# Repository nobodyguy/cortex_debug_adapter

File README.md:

# cortex_debug_adapter
Adapts the standard 10-pin 0.05" pitch ARM Cortex JTAG/SWD connector to a 7-pin 0.1" pitch row.\
Works great with the [greyhound probe](https://github.com/nobodyguy/greyhound_probe).

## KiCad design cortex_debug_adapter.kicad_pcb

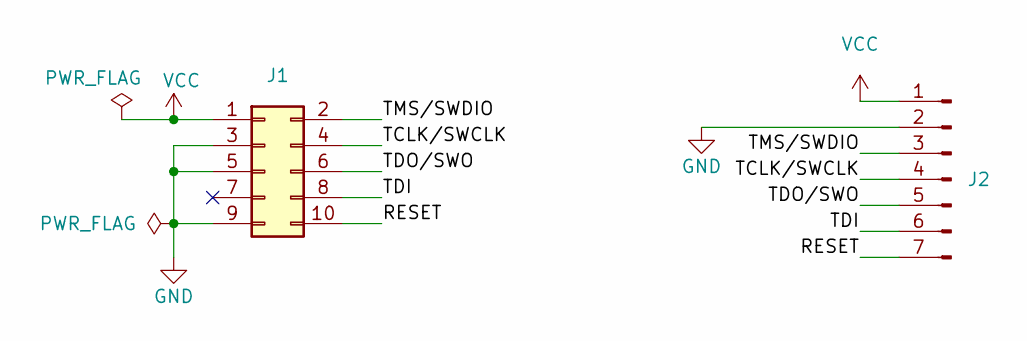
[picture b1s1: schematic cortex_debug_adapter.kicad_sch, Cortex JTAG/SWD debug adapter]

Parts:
J1: Conn_02x05_Odd_Even; PinHeader_2x05_P1.27mm_Vertical; LCSC Part C2935883
J2: Conn_01x07_Male; PinHeader_1x07_P2.54mm_Vertical; LCSC Part C2935932

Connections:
/RESET: J1.10, J2.7
/TCLK/SWCLK: J1.4, J2.4
/TDI: J1.8, J2.6
/TDO/SWO: J1.6, J2.5
/TMS/SWDIO: J1.2, J2.3
GND: J1.3, J1.5, J1.9, J2.2
VCC: J1.1, J2.1

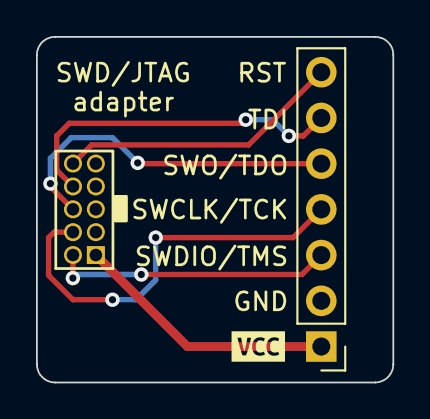
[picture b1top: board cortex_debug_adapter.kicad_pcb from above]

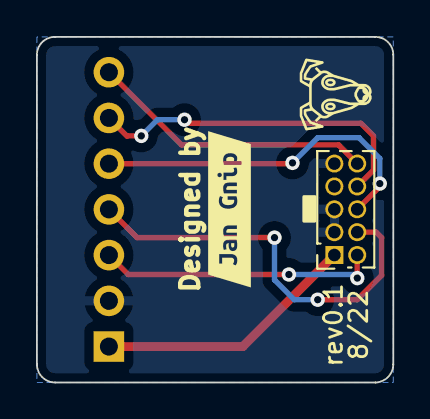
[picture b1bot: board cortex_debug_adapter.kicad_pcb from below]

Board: 2 copper layers, 19.8 x 19.2 mm, 4 parts (2 on the bottom side), 7 nets.

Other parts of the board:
kibuzzard-62A19C5B: G***; kibuzzard-62A19C5B
kibuzzard-630691B0: G***; kibuzzard-630691B0

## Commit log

2022-08-23 Schematic part done
2022-08-24 PCB done
2022-08-24 Added render
2022-08-24 Finished PCB silkscreen
2022-08-24 Added exported gerbers
2022-08-25 Redesign because of better connector orientation
2022-08-25 Better colors in 3D render
